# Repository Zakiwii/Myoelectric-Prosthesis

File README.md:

[README.md](https://github.com/user-attachments/files/29821908/README.md)
# EMG Myoelectric Prosthesis

A myoelectric wrist/hand prosthesis controlled by EMG (electromyography) signals, developed as a Master's thesis (PFE) project at USTHB (Université des Sciences et de la Technologie Houari Boumediene), Algiers.

> 🎓 Defended with highest honors (*mention très bien*).

<!-- Replace the line above with your own image path once uploaded, or add more images below -->

## Overview

This project implements a low-cost, functional prosthetic wrist that translates forearm EMG muscle signals into automated wrist movements via a servo-driven mechanism. The goal was to build an accessible, reproducible design using widely available components rather than expensive commercial EMG modules.

## How It Works

1. An EMG sensor module picks up electrical activity from the forearm muscles (bipolar signal, powered by a symmetric ±9V supply).
2. The raw signal is conditioned and thresholded to detect muscle contraction events.
3. A Digispark ATtiny85 microcontroller reads the processed signal and generates a manual PWM control signal.
4. An MG996R servo motor executes the corresponding wrist movement.
5. Power is regulated through an LM2596 buck converter for stable operation.

## Hardware

- **Microcontroller:** Digispark ATtiny85
- **EMG sensing:** EMG module (MyoWare-style), symmetric ±9V supply
- **Actuation:** MG996R servo motor
- **Power regulation:** LM2596 buck converter
- **PCB:** Custom-designed in KiCad (schematic capture, DRC, ground planes, Gerber export)
- **Enclosure:** 3D-modeled in Fusion 360, 3D-printed

## Repository Structure

```
prothese-emg/
├── hardware/
│   ├── kicad/          # Schematic, PCB layout, Gerber files
│   └── enclosure/      # Fusion 360 / STEP / STL files
├── firmware/
│   └── attiny85/        # C/C++ firmware for the ATtiny85
├── docs/
│   ├── thesis.pdf        # Full thesis document (French)
│   └── diagrams/         # System architecture diagrams
└── media/
    └── photos, demo video
```

## Firmware

Written in C/C++ for the ATtiny85 (Digispark board), including manual PWM generation for servo control and EMG signal threshold calibration logic.

## Skills & Tools Used

`KiCad` · `Fusion 360` · `Arduino IDE / Micronucleus` · `C/C++` · `EMG signal processing` · `PCB design (DRC, Gerber export)`

## Author

**Senouci Abderraouf Zaki** — M2 Electronics and Embedded Systems, USTHB.

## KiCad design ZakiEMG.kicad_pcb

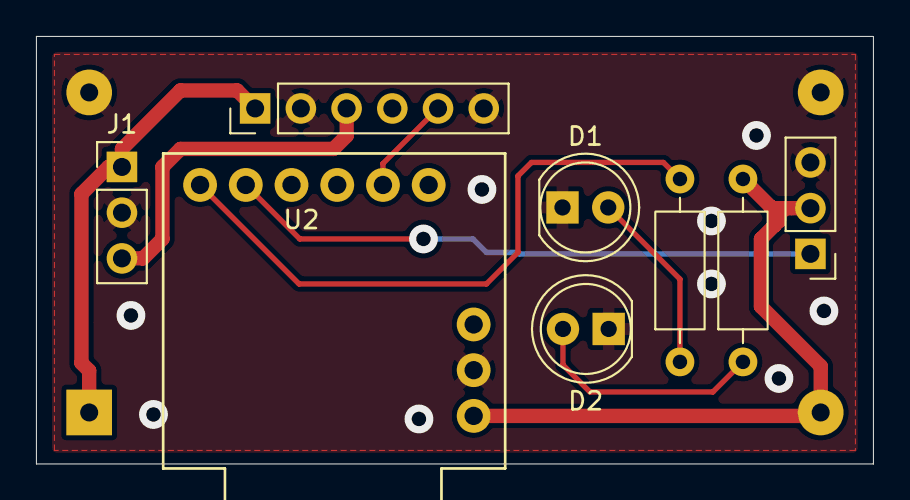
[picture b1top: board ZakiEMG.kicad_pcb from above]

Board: 2 copper layers, 46.5 x 23.8 mm, 9 parts (1 on the bottom side), 9 nets.

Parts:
D1, D2: LED; LED_D5.0mm
J1: Power_in; PinHeader_1x03_P2.54mm_Vertical
J2: EMG; PinHeader_1x06_P2.54mm_Vertical
J3: Servo_out; PinHeader_1x03_P2.54mm_Vertical
R1, R2: 25; R_Axial_DIN0207_L6.3mm_D2.5mm_P10.16mm_Horizontal
U1: LM2596; YAAJ_DCDC_StepDown_LM2596
U2: Digispark

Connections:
+5V: J3.2, R2.2, U1.4 (Vout), U2.9 (5V)
+9V: J1.1, J2.1, U1.1 (Vin)
-9V: J1.3, J2.3
/EMG_Sign: J2.5, U2.2 (D1/PWM1)
/LED_Sig: R1.2, U2.6 (D5/A0)
/Servo_Sig: J3.1, U2.5 (D4/PWM4)
GND: D1.1 (K), D2.1 (K), J1.2, J2.2, J2.6, J3.3, U1.2 (GND), U1.3 (GND), U2.8 (GND)
unnamed: D1.2 (A), R1.1
unnamed: D2.2 (A), R2.1
